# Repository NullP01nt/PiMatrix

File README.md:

# PiMatrix

## Authors
* Xander Bos
* Nikolaj Iversen

## About

PiMatrix is a project in which we combine the concepts of distributed computing
with external IO by use of Raspberry Pis, a messaging library called ZeroMQ and
wiringPi.

This combines to be a system where input is given by remote input publishers
and a single subscriber by the use of a Message Broker.

Inside the eagle folder, there is a design for an add-on board suited for a
Raspberry Pi 2+. This add-on board includes 2 8x8 LED matrices to form a
complete 16x8 LED matrix display.

The software side of things is partly managed by the following services:
* Avahi-daemon (mDNS)
* DNSMasq (DHCP)

To be on the safe side, both Avahi-daemon and DNSMasq have been set to only use
local ethernet devices. Documentation can be found in the relevant man-pages.

The source folder includes the following applications:
* MatrixSnake
* MessageBroker
* Mousepublisher
* JoystickPublisher

Our setup consists of the following systems:
The setup consists of the following systems:
* Laptop 
  * Avahi-daemon (broker.local)
  * DNSMasq 
* Raspberry Pi 2 with add-on board 
  * Avahi-daemon (screenpi.local)
* Raspberry PI 2 with mouse 
  * Avahi-daemon (mousepi.local)

#### Setup guide for the project ####

#### On the laptop ####
```bash
su
apt-add-repository ppa:segf4ult/zeromq
apt update
apt install build-essential git-core qttools5-dev \
  libqt5core5a avahi-daemon pkg-config cppzmq
exit
git clone https://github.com/NullP01nt/PiMatrix.git
cd PiMatrix/src/MessageBroker
qmake
make
./MessageBroker &
```

##### If a PS3 controller is desired, connect it to the laptop
[check out setup guide] (https://help.ubuntu.com/community/Sixaxis)
```bash
echo "
[publisher]
host=broker.local
topic=CTRL
port=55554
[device]
device_name=/dev/input/js0
" > ~/.config/SDU-EMB4/P3_JOYPUB.conf
cd -
cd PiMatrix/src/JoystickPublisher
qmake
make
./JoystickPublisher &
```

#### on the pi's ####
```bash
sudo su
apt-add-repository ppa:segf4ult/zeromq
apt update
apt install build-essential git-core qttools5-dev \
  libqt5core5a avahi-daemon pkg-config cppzmq
exit
git clone git://git.drogon.net/wiringPi
cd wiringPi
./build
cd -
git clone https://github.com/NullP01nt/PiMatrix.git
cd PiMatrix
```

##### On the MousePi #####
```bash
cd src/MousePublisher
qmake
make
##### plug in mouse #####
MOUSE=/dev/input/$(ls -lc /dev/input/by-path/ | 
                   # l to see symbolic links, c for sorting
                   grep event-mouse | # select the event-mouse
                   head -n 1 | # if there is more than one, 
                               # pick the one most recently plugged in.
                   rev | # reverse to get the last
                   cut -d '/' -f 1 | #entry of '/'
                   rev ) # reverse again to make it readable
sudo chmod +r $MOUSE
echo "
[device]
mouse=$MOUSE
[publisher]
host=broker.local
topic=CTRL
port=55554
" > ~/.config/SDU-EMB4/P3_MOUSEPUB.conf
echo "PATH=\$PATH:$pwd" >> ~/.bashrc
source ~/.bashrc
MousePublisher
```

##### On the ScreenPi #####
```bash
cd src/MatrixSnake
qmake
make
echo "
[subscriber]
host=broker.local
topic=CTRL
port=55555
" > ~/.config/SDU-EMB4/P3_MATSNAKE.conf
echo "PATH=\$PATH:$pwd" >> ~/.bashrc
source ~/.bashrc
MatrixSnake
```

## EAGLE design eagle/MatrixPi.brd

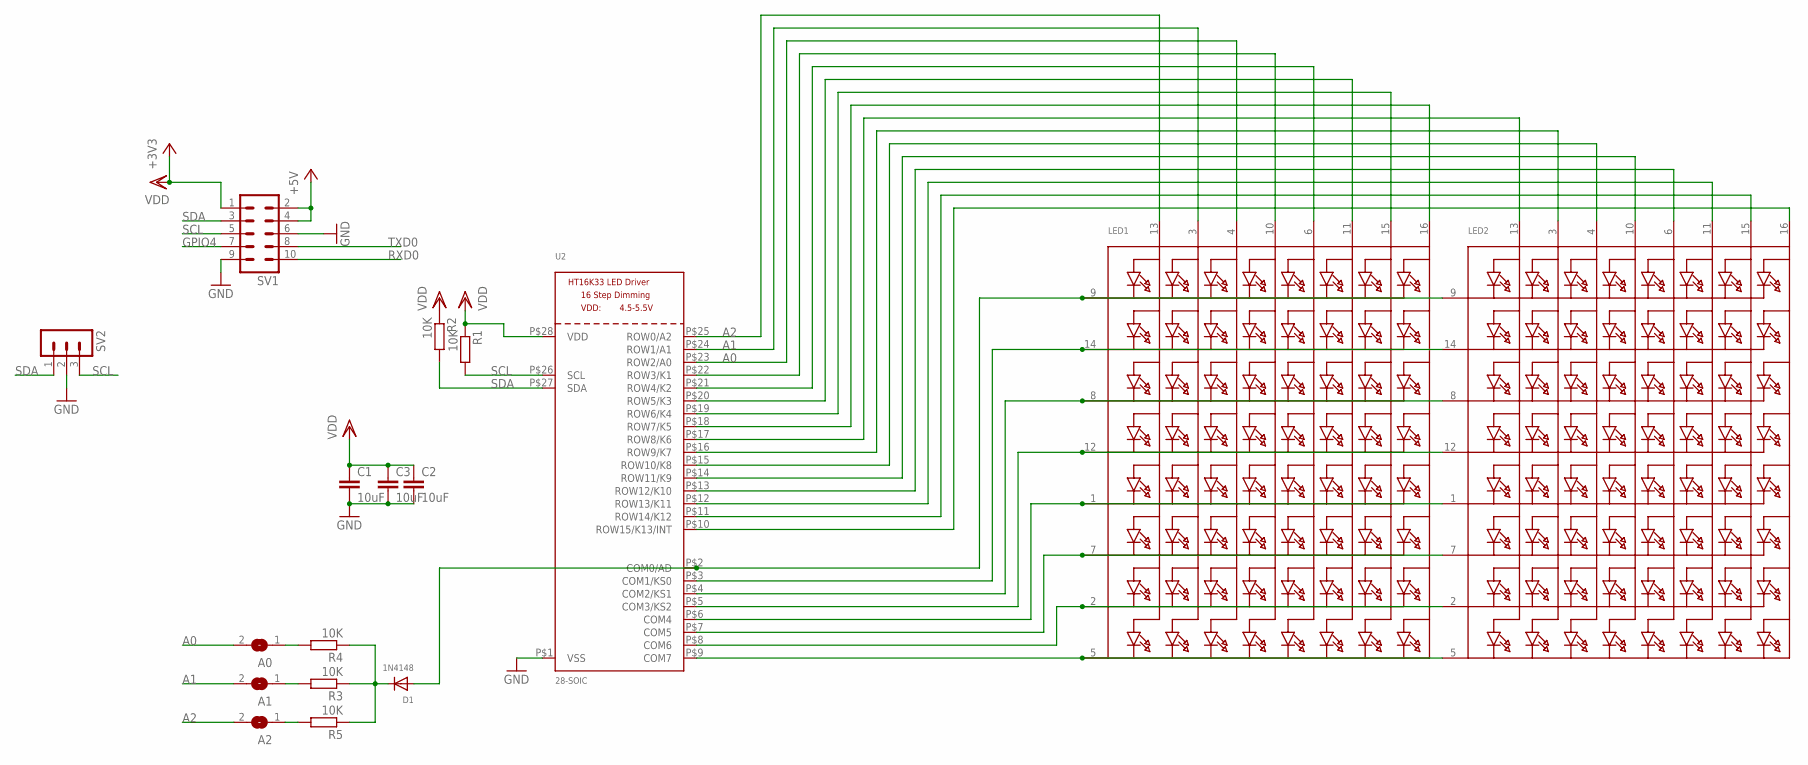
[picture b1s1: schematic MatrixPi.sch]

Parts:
A0, A1, A2: SOLDERJUMPERREFLOW_NOPASTE; SOLDERJUMPER_REFLOW_NOPASTE
C1, C2, C3: 10uF; C0805
D1: 1N4148; SOD-323F
LED1, LED2: MATRIX_8X8_ROWCATHODE; TA15-11CGKWA
R1, R2, R3, R4, R5: 10K; M0805
SV1: MA05-2
SV2: MA03-1
U2: 28-SOIC; SOP28_300MIL

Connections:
+5V: SV1.2, SV1.4
A0: A0.2, LED1.4 (A3), U2.P$23 (ROW2/A0)
A1: A1.2, LED1.3 (A2), U2.P$24 (ROW1/A1)
A2: A2.2, LED1.13 (A1), U2.P$25 (ROW0/A2)
GND: C1.2, C2.2, C3.2, SV1.6, SV1.9, SV2.2, U2.P$1 (VSS)
GPIO4: SV1.7
unnamed: LED1.5 (K8), LED2.5 (K8), U2.P$9 (COM7)
unnamed: LED1.2 (K7), LED2.2 (K7), U2.P$8 (COM6)
unnamed: LED1.7 (K6), LED2.7 (K6), U2.P$7 (COM5)
unnamed: LED1.1 (K5), LED2.1 (K5), U2.P$6 (COM4)
unnamed: LED1.12 (K4), LED2.12 (K4), U2.P$5 (COM3/KS2)
unnamed: LED1.8 (K3), LED2.8 (K3), U2.P$4 (COM2/KS1)
unnamed: LED1.14 (K2), LED2.14 (K2), U2.P$3 (COM1/KS0)
unnamed: D1.A, LED1.9 (K1), LED2.9 (K1), U2.P$2 (COM0/AD)
unnamed: A2.1, R5.2
unnamed: LED2.15 (A7), U2.P$11 (ROW14/K12)
unnamed: LED2.11 (A6), U2.P$12 (ROW13/K11)
unnamed: LED2.16 (A8), U2.P$10 (ROW15/K13/INT)
unnamed: D1.C, R3.1, R4.1, R5.1
unnamed: A1.1, R3.2
unnamed: A0.1, R4.2
unnamed: LED1.16 (A8), U2.P$18 (ROW7/K5)
unnamed: LED1.15 (A7), U2.P$19 (ROW6/K4)
unnamed: LED1.6 (A5), U2.P$21 (ROW4/K2)
unnamed: LED1.10 (A4), U2.P$22 (ROW3/K1)
unnamed: LED1.11 (A6), U2.P$20 (ROW5/K3)
unnamed: LED2.13 (A1), U2.P$17 (ROW8/K6)
unnamed: LED2.3 (A2), U2.P$16 (ROW9/K7)
unnamed: LED2.10 (A4), U2.P$14 (ROW11/K9)
unnamed: LED2.4 (A3), U2.P$15 (ROW10/K8)
unnamed: LED2.6 (A5), U2.P$13 (ROW12/K10)
RXD0: SV1.10
SCL: R1.2, SV1.5, SV2.3, U2.P$26 (SCL)
SDA: R2.2, SV1.3, SV2.1, U2.P$27 (SDA)
TXD0: SV1.8
VDD: C1.1, C2.1, C3.1, R1.1, R2.1, SV1.1, U2.P$28 (VDD)

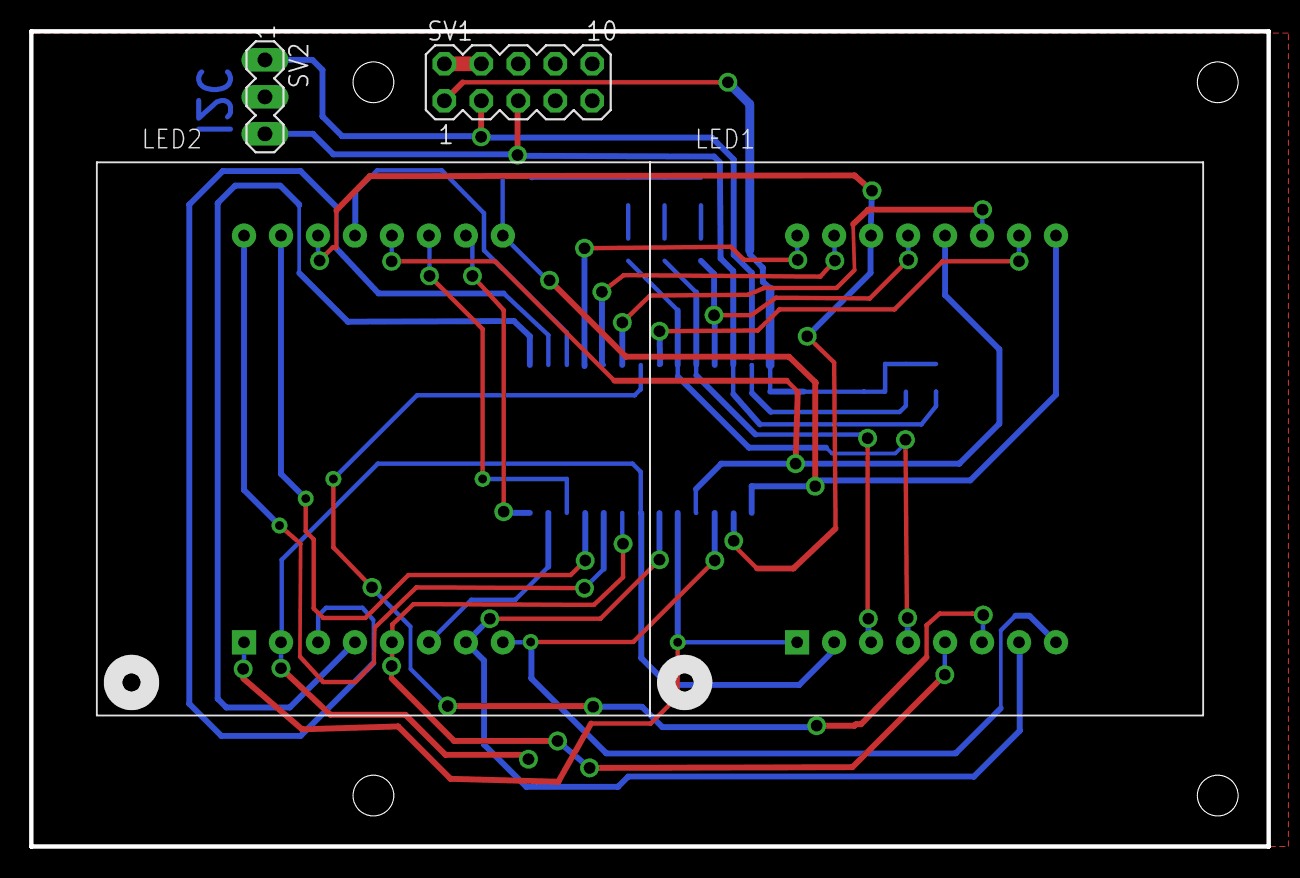
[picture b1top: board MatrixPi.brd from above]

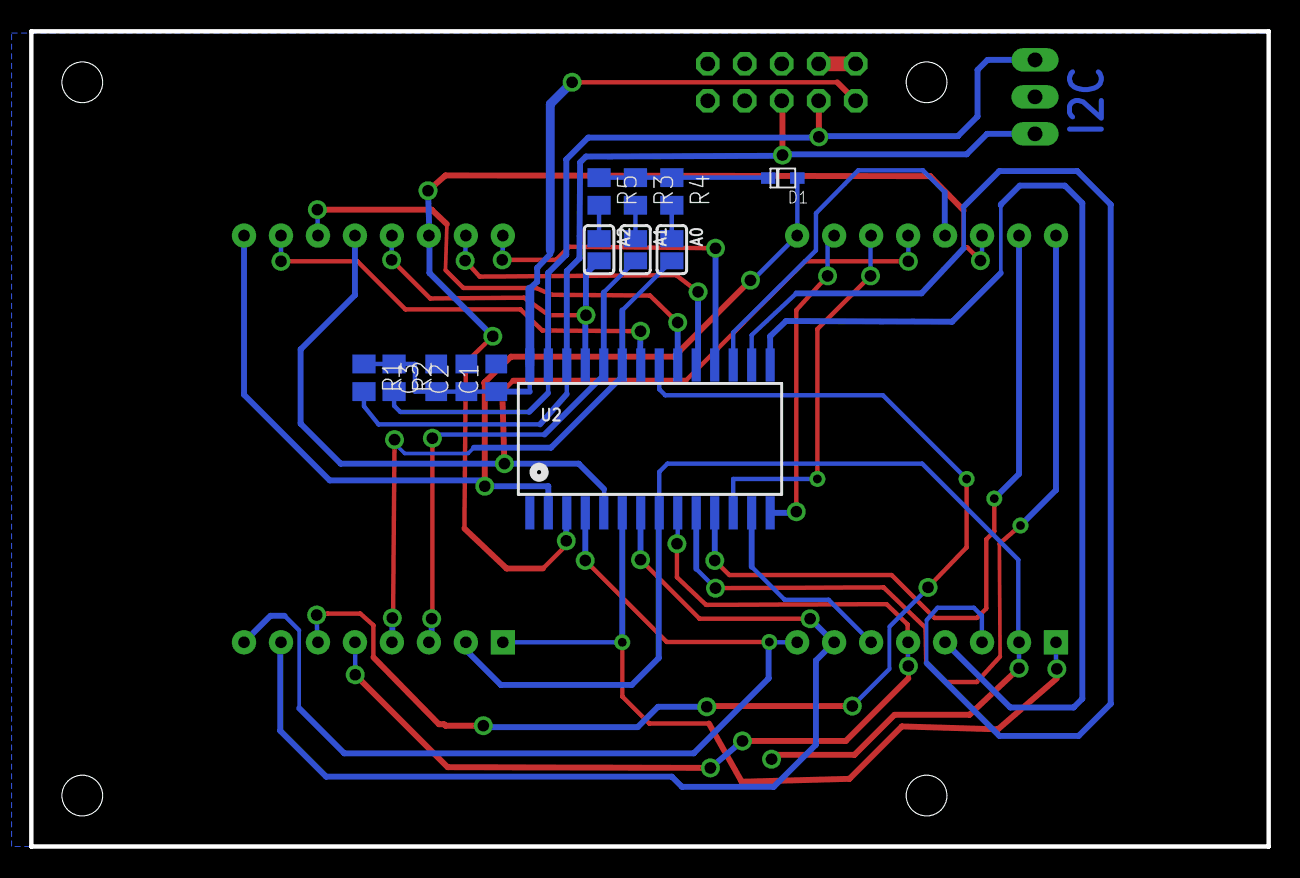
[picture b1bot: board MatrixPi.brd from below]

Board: 2 copper layers, 85.0 x 56.0 mm, 17 parts (13 on the bottom side), 33 nets.

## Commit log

2016-05-06 Added paths for various project files, modified gitignore to include rules for C++, Qt and Eagle
2016-05-07 Started work on matrix code
2016-05-07 Added more functionality
2016-05-07 Making preparations to go for hardware support
2016-05-09 added a todo for next time
2016-05-10 Made eagle files
2016-05-10 Separated gitignores, made a toplevel subdirs project, added JSTest project
2016-05-11 ads mouse driver
2016-05-11 Make the mouse application read a environment variable
2016-05-11 Added WIP eagle board and schematic
2016-05-11 Revised board
2016-05-11 This adds the subscriber/publisher model to mouse reading
2016-05-11 Board revisions
2016-05-11 Board revision
2016-05-11 Eagle files revision number big
2016-05-11 Board revision big+1
2016-05-11 Board revision big+2
2016-05-11 Board revision big+3
2016-05-11 Board revision big+4
2016-05-11 Board revision big+5
2016-05-11 Board revision big+6
2016-05-11 This adds a snake game and ways to manipulate individual pixels
2016-05-17 snake is now playable
2016-05-20 Added Extended project, which includes msg_types header file etc.
2016-05-20 Added Extended as a subproject of src
2016-05-20 Renamed files
2016-05-20 Fixed the msg broker and set up the publisher and subscriber to connect to it
2016-05-20 updated board
2016-05-20 Working on QSubscriber to have event-driven things working
2016-05-21 Important lesson: /dev/input/mice and /dev/input/event* does not use the same format. The application worked fine as it was
2016-05-21 event to game subscriber
2016-05-21 Revised several projects to build cleanly, working on QSubscriber
2016-05-21 The Qsub class is the working example one thread that reads the correct message type and sends it as a Qtsignal., The receiver class reads over ØMQ, the worker class prints the data. A full example o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
2016-05-21 created game_handler, which takes the package and plays the game
2016-05-21 the mouse app now reads the config file and sends with the new message type.
2016-05-21 made a input server which reads the file in a thread, so both input devices can be run at the same time.
2016-05-21 added gitignore
2016-05-21 moved the app.h into include, so every application can use the same config file
2016-05-22 Started cleanup
2016-05-22 Cleaning up big-time
2016-05-22 Final cleanup
2016-05-22 Final cleanup +1
2016-05-22 Replaced global app.h files with local app.h files
2016-05-22 Working on JoystickPublisher
2016-05-22 Start refactoring JoystickPublisher
2016-05-22 Started refactoring MousePublisher and JoystickPublisher
2016-05-22 Work on refactoring MousePublisher
2016-05-22 Refactored MousePublisher
2016-05-22 Renaming started
2016-05-22 i2ctest added
2016-05-22 updated matrix to work with i2c, made timeout on snake game to turn off leds
2016-05-22 Revised JoystickPublisher, MousePublisher and joystick.h
2016-05-22 Made JoystickPublisher quit safely
2016-05-22 Made MousePublisher and JoystickPublisher exit cleanly
2016-05-22 Tried to fix recursive termination of thread on MousePublisher
2016-05-22 Added joystick_event_handler to MatrixSnake
2016-05-22 Added joystick integration, fixed matrix display bugs, fixed game state switching etc.
2016-05-22 the debug is now correct
2016-05-22 commented out debug as it should use the leds on the pi
2016-05-23 Revised mouse_event_handler and added mouse defines to include/mouse.h
2016-05-23 Removed i2ctest
2016-05-23 Mod README.md
2016-05-23 Mod Readme
2016-05-23 Renamed MsgBroker to MessageBroker
2016-05-23 Modified Readme
2016-05-23 readme
2016-05-23 Fixed JOYPUB conf in README.md
2016-05-23 Capped README.md at 80 chars
2016-05-23 Added more newlines to README.md
2016-05-23 Made note of eth0 lockdown
2016-05-23 Added brightness control to MatrixSnake
